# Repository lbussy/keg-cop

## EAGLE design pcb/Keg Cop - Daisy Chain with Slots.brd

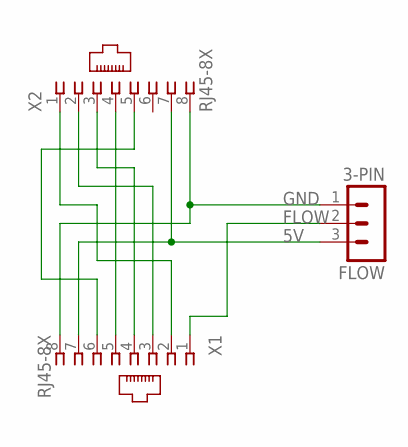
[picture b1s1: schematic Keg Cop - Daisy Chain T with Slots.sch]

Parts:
FLOW: 3-PIN; HDR-3_VERT
X1, X2: RJ45-8X; RJ45-NO-SHIELD

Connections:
5V: FLOW.3, X1.7, X2.7
FLOW: FLOW.2, X1.1
GND: FLOW.1, X1.8, X2.8
unnamed: X1.2, X2.1
unnamed: X1.3, X2.2
unnamed: X1.4, X2.3
unnamed: X1.5, X2.4
unnamed: X1.6, X2.5

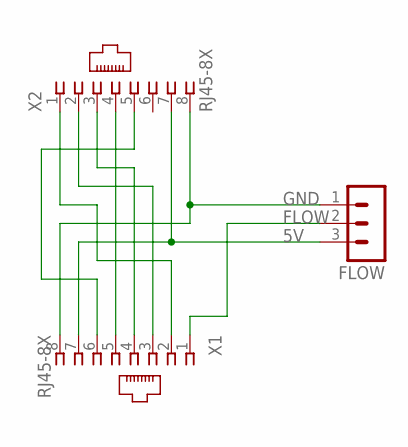
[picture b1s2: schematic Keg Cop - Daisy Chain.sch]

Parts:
FLOW: HDR-3; HDR-3_VERT
X1, X2: RJ45-8X; RJ45-NO-SHIELD

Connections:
5V: FLOW.3, X1.7, X2.7
FLOW: FLOW.2, X1.1
GND: FLOW.1, X1.8, X2.8
unnamed: X1.2, X2.1
unnamed: X1.3, X2.2
unnamed: X1.4, X2.3
unnamed: X1.5, X2.4
unnamed: X1.6, X2.5

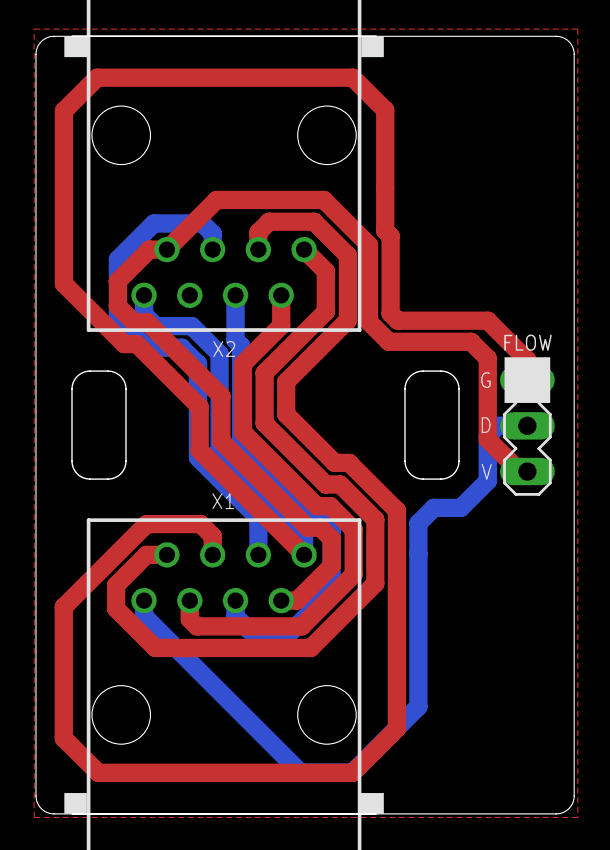
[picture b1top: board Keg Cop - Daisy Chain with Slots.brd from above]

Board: 2 copper layers, 29.9 x 43.2 mm, 3 parts (0 on the bottom side), 8 nets.

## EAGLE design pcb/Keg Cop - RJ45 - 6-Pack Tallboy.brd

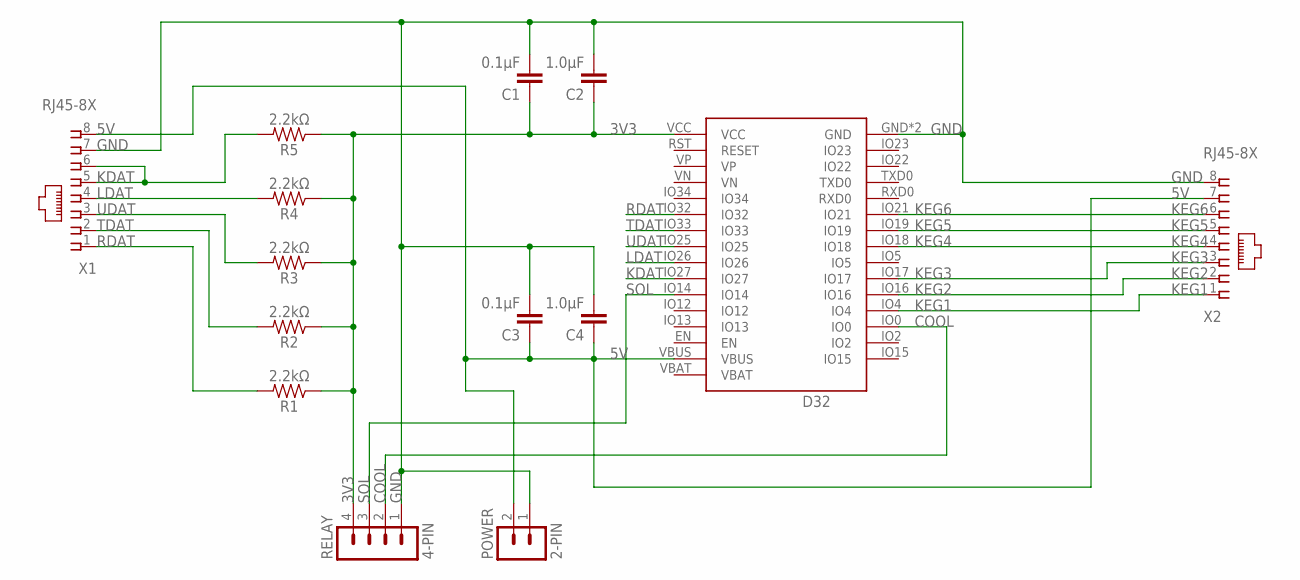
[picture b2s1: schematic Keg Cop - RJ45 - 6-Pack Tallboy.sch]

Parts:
C1, C3: 0.1μF; CAP_PTH-2.54
C2, C4: 1.0μF; CAP_PTH-2.54
D32: Lolin D32; D32_NO_BATT
POWER: 2-PIN; HDR-2_VERT
R1, R2, R3, R4, R5: 2.2kΩ; AXIAL-0.3
RELAY: 4-PIN; MA04-1
X1, X2: RJ45-8X; RJ45-NO-SHIELD

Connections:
3V3: C1.1, C2.1, D32.VCC, R1.P$1 (1), R2.P$1 (1), R3.P$1 (1), R4.P$1 (1), R5.P$1 (1), RELAY.4
5V: C3.1, C4.1, D32.VBUS, POWER.2, X1.8, X2.7
COOL: D32.IO0, RELAY.2
GND: C1.2, C2.2, C3.2, C4.2, D32.GND, D32.GND2 (GND), POWER.1, RELAY.1, X1.7, X2.8
KDAT: D32.IO27, R5.P$2 (2), X1.5, X1.6
KEG1: D32.IO4, X2.1
KEG2: D32.IO16, X2.2
KEG3: D32.IO17, X2.3
KEG4: D32.IO18, X2.4
KEG5: D32.IO19, X2.5
KEG6: D32.IO21, X2.6
LDAT: D32.IO26, R4.P$2 (2), X1.4
RDAT: D32.IO32, R1.P$2 (2), X1.1
SOL: D32.IO14, RELAY.3
TDAT: D32.IO33, R2.P$2 (2), X1.2
UDAT: D32.IO25, R3.P$2 (2), X1.3

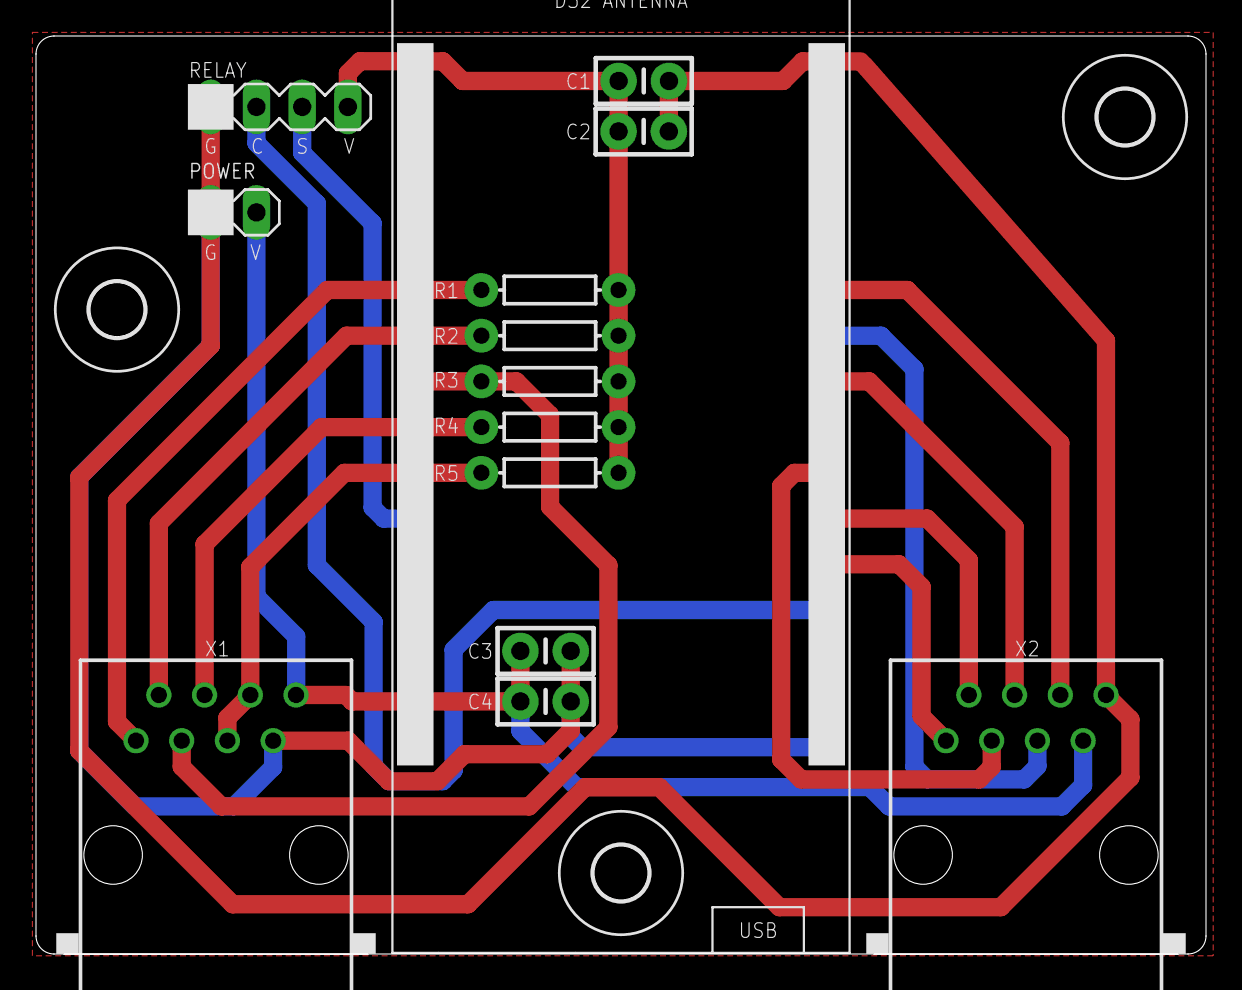
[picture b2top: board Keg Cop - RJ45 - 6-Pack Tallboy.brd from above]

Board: 2 copper layers, 65.0 x 51.0 mm, 17 parts (0 on the bottom side), 16 nets.

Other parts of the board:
U$1, U$2, U$3: 3,0

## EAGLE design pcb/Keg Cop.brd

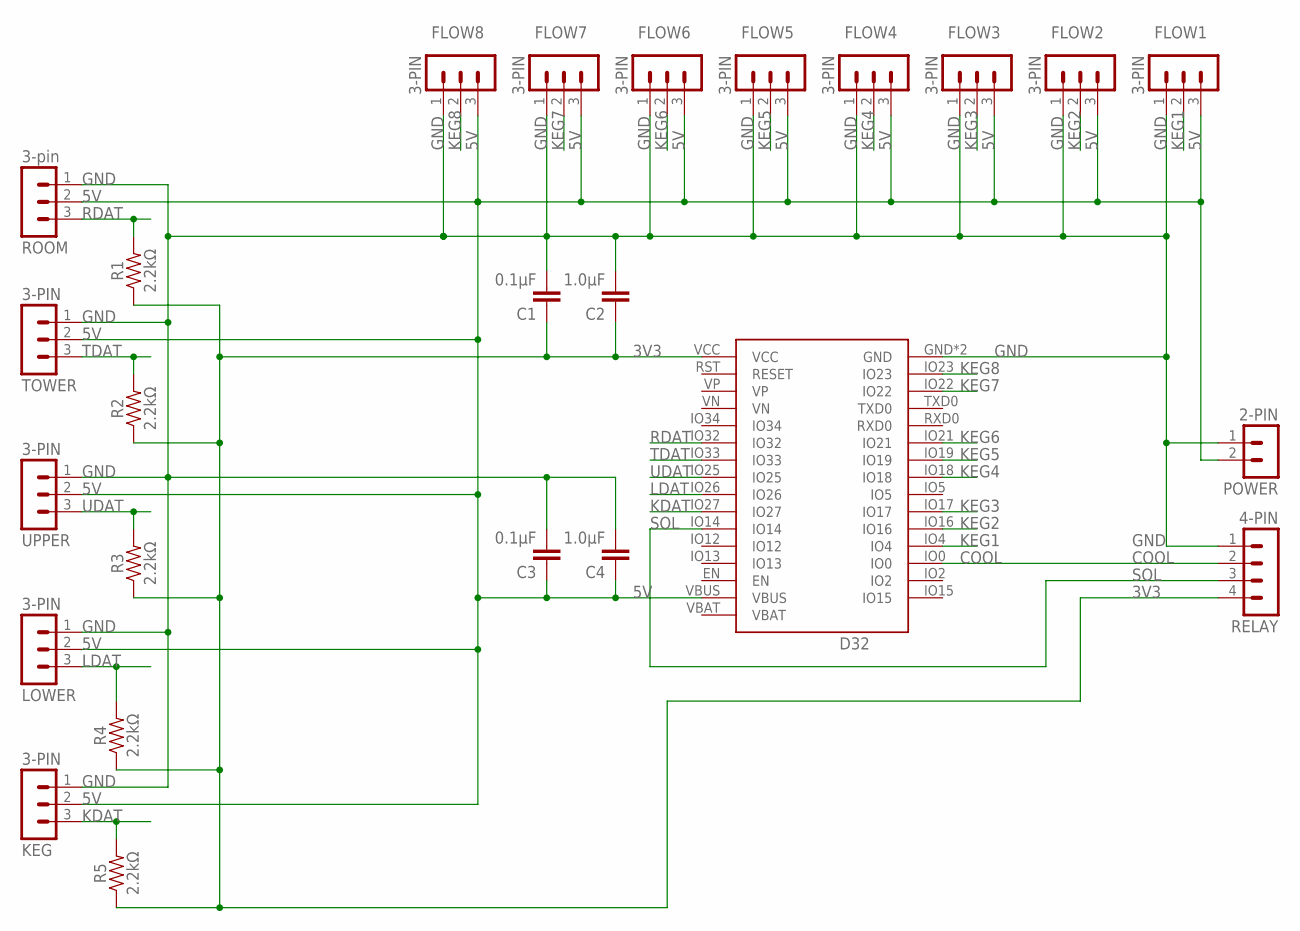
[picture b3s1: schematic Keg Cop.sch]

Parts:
C1, C3: 0.1μF; CAP_PTH-2.54
C2, C4: 1.0μF; CAP_PTH-2.54
D32: WEMOS-D32D32_NO_BATT; D32_NO_BATT
FLOW1, FLOW2, FLOW3, FLOW4, FLOW5, FLOW6, FLOW7, FLOW8: 3-PIN; MA03-1
KEG: 3-PIN; MA03-1
LOWER: 3-PIN; MA03-1
POWER: 2-PIN; HDR-2_VERT
R1, R2, R3, R4, R5: 2.2kΩ; AXIAL-0.3
RELAY: 4-PIN; MA04-1
ROOM: 3-pin; MA03-1
TOWER: 3-PIN; MA03-1
UPPER: 3-PIN; MA03-1

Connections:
3V3: C1.1, C2.1, D32.VCC, R1.P$1 (1), R2.P$1 (1), R3.P$1 (1), R4.P$1 (1), R5.P$1 (1), RELAY.4
5V: C3.1, C4.1, D32.VBUS, FLOW1.3, FLOW2.3, FLOW3.3, FLOW4.3, FLOW5.3, FLOW6.3, FLOW7.3, FLOW8.3, KEG.2, LOWER.2, POWER.2, ROOM.2, TOWER.2, UPPER.2
COOL: D32.IO0, RELAY.2
GND: C1.2, C2.2, C3.2, C4.2, D32.GND, D32.GND2 (GND), FLOW1.1, FLOW2.1, FLOW3.1, FLOW4.1, FLOW5.1, FLOW6.1, FLOW7.1, FLOW8.1, KEG.1, LOWER.1, POWER.1, RELAY.1, ROOM.1, TOWER.1, UPPER.1
KDAT: D32.IO27, KEG.3, R5.P$2 (2)
KEG1: D32.IO4, FLOW1.2
KEG2: D32.IO16, FLOW2.2
KEG3: D32.IO17, FLOW3.2
KEG4: D32.IO18, FLOW4.2
KEG5: D32.IO19, FLOW5.2
KEG6: D32.IO21, FLOW6.2
KEG7: D32.IO22, FLOW7.2
KEG8: D32.IO23, FLOW8.2
LDAT: D32.IO26, LOWER.3, R4.P$2 (2)
RDAT: D32.IO32, R1.P$2 (2), ROOM.3
SOL: D32.IO14, RELAY.3
TDAT: D32.IO33, R2.P$2 (2), TOWER.3
UDAT: D32.IO25, R3.P$2 (2), UPPER.3

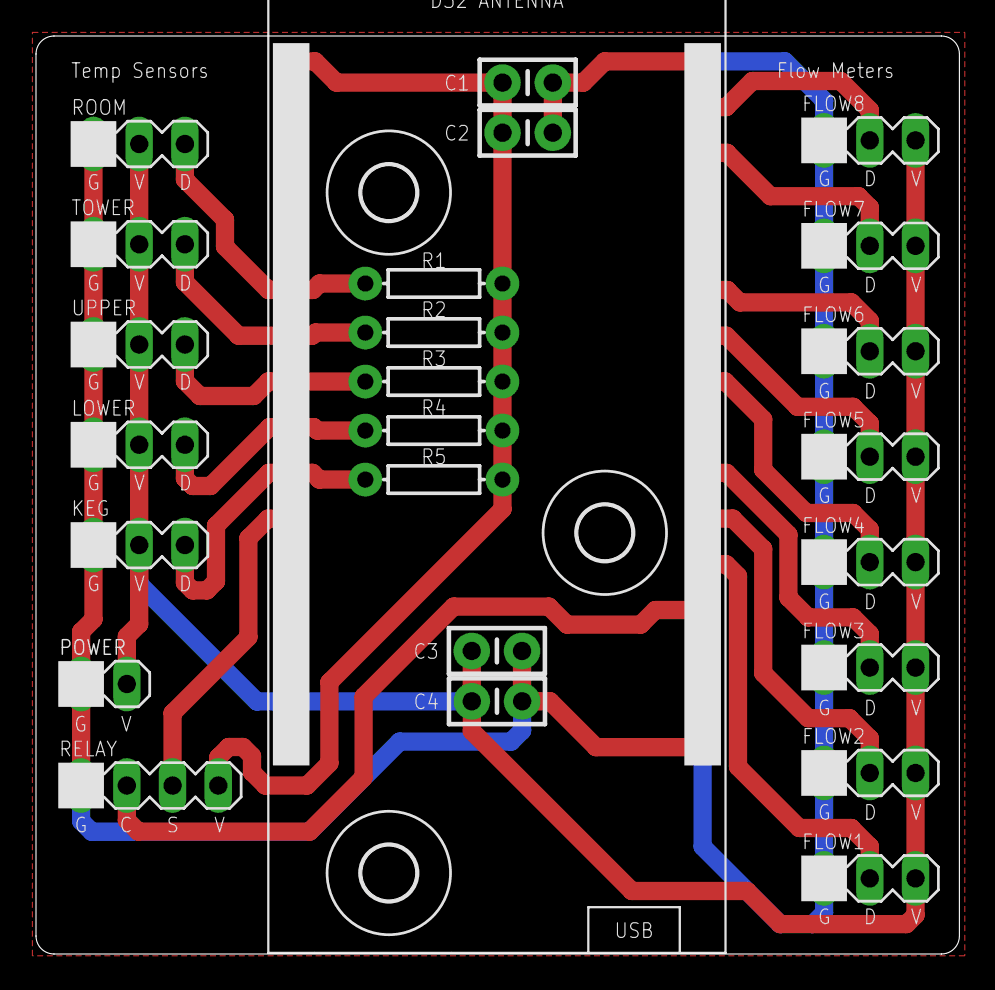
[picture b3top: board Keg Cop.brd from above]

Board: 2 copper layers, 51.3 x 51.0 mm, 28 parts (0 on the bottom side), 18 nets.

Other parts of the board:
U$1, U$2, U$3: 3,0

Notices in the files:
parts and their libraries:
SparkFun-Resistors: Licensing: Creative Commons ShareAlike 4.0 International - https://creativecommons.org/licenses/by-sa/4.0
